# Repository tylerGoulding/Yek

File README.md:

# YEK
Yek is a prototype of an on-hand password manager that redefines how users interact with account safety and passwords on a laptop computer. It is an embedded device that acts as your personal butler to memorize passwords. With a yek device and a fingerprint scan, you can login to any of your accounts by connecting to any computer device through a bluetooth connection. Yek  acts as a keyboard and types in your login information (username and password) to the selected textbox of a login page, so that you do not have to remember your unique and strong passwords. It can fit in your pocket just like a physical keychain, and yet it can hold 63 of your accounts through a computer application.

## Team
- Fatema Almeshqab
- Tyler Goulding
- Matt Chu

## Code
When prototyping, we developed in Arduino then ported it to AVR C. We have included both for your convenience.

## PCB
The pcb was designed in Eagle. There is one error in the PCB if you are planning to send it out (or printing it in house if that's your slice of pie). The pins on the Battery JST plug are flipped. This is not a major issue but change it if you would like. We did not so that the professors could see our the equivalent PCB we printed.
## Computer Application
The computer application was written in Java and is available as a runnable .jar file that works on Windows, Mac, or Linux, and just requires that Java 8 be installed. The app, uses a library called jSerialComm to communicate with the Yek through a serial port connection.

## Building the Yek
### If you want to use Arduino
To build with Arduino:
Download the following libraries:

U8g2 Screen Library:
> https://github.com/olikraus/U8g2_Arduino

FRAM Library: 

> https://github.com/adafruit/Adafruit_FRAM_I2C

Fingerprint scanner:
> https://github.com/sparkfun/Fingerprint_Scanner-TTL

Bluefruit library:
> https://github.com/adafruit/Adafruit_BluefruitLE_nRF51

Open Arduino and compile the .ino in the folder Yek_arduino

### If you want to use GCC
Use the code in Yek_firmware folder

To build with GCC:

- install avr-gcc (GCC) 7.2.0 using your favorite package manager (this will take 2 hours... sorry)
- download LUFA
- update the path to lufa into makefile
- run make in the folder

## Acknowledgements
* Dean Camera, for LUFA.
* Adafruit (author hathach), for their parts and their BLE library
* Josh Hawley, for his FPS library
* Arduino, for their Print class and Stream class
* Olikraus, for the screen library and compressed fonts
* Zak Kemble, for a AVR implementation of millis
* Mike DiBacco, for helping us lasercut the case
* Some random dude at the Makerspace who helped me 3d print

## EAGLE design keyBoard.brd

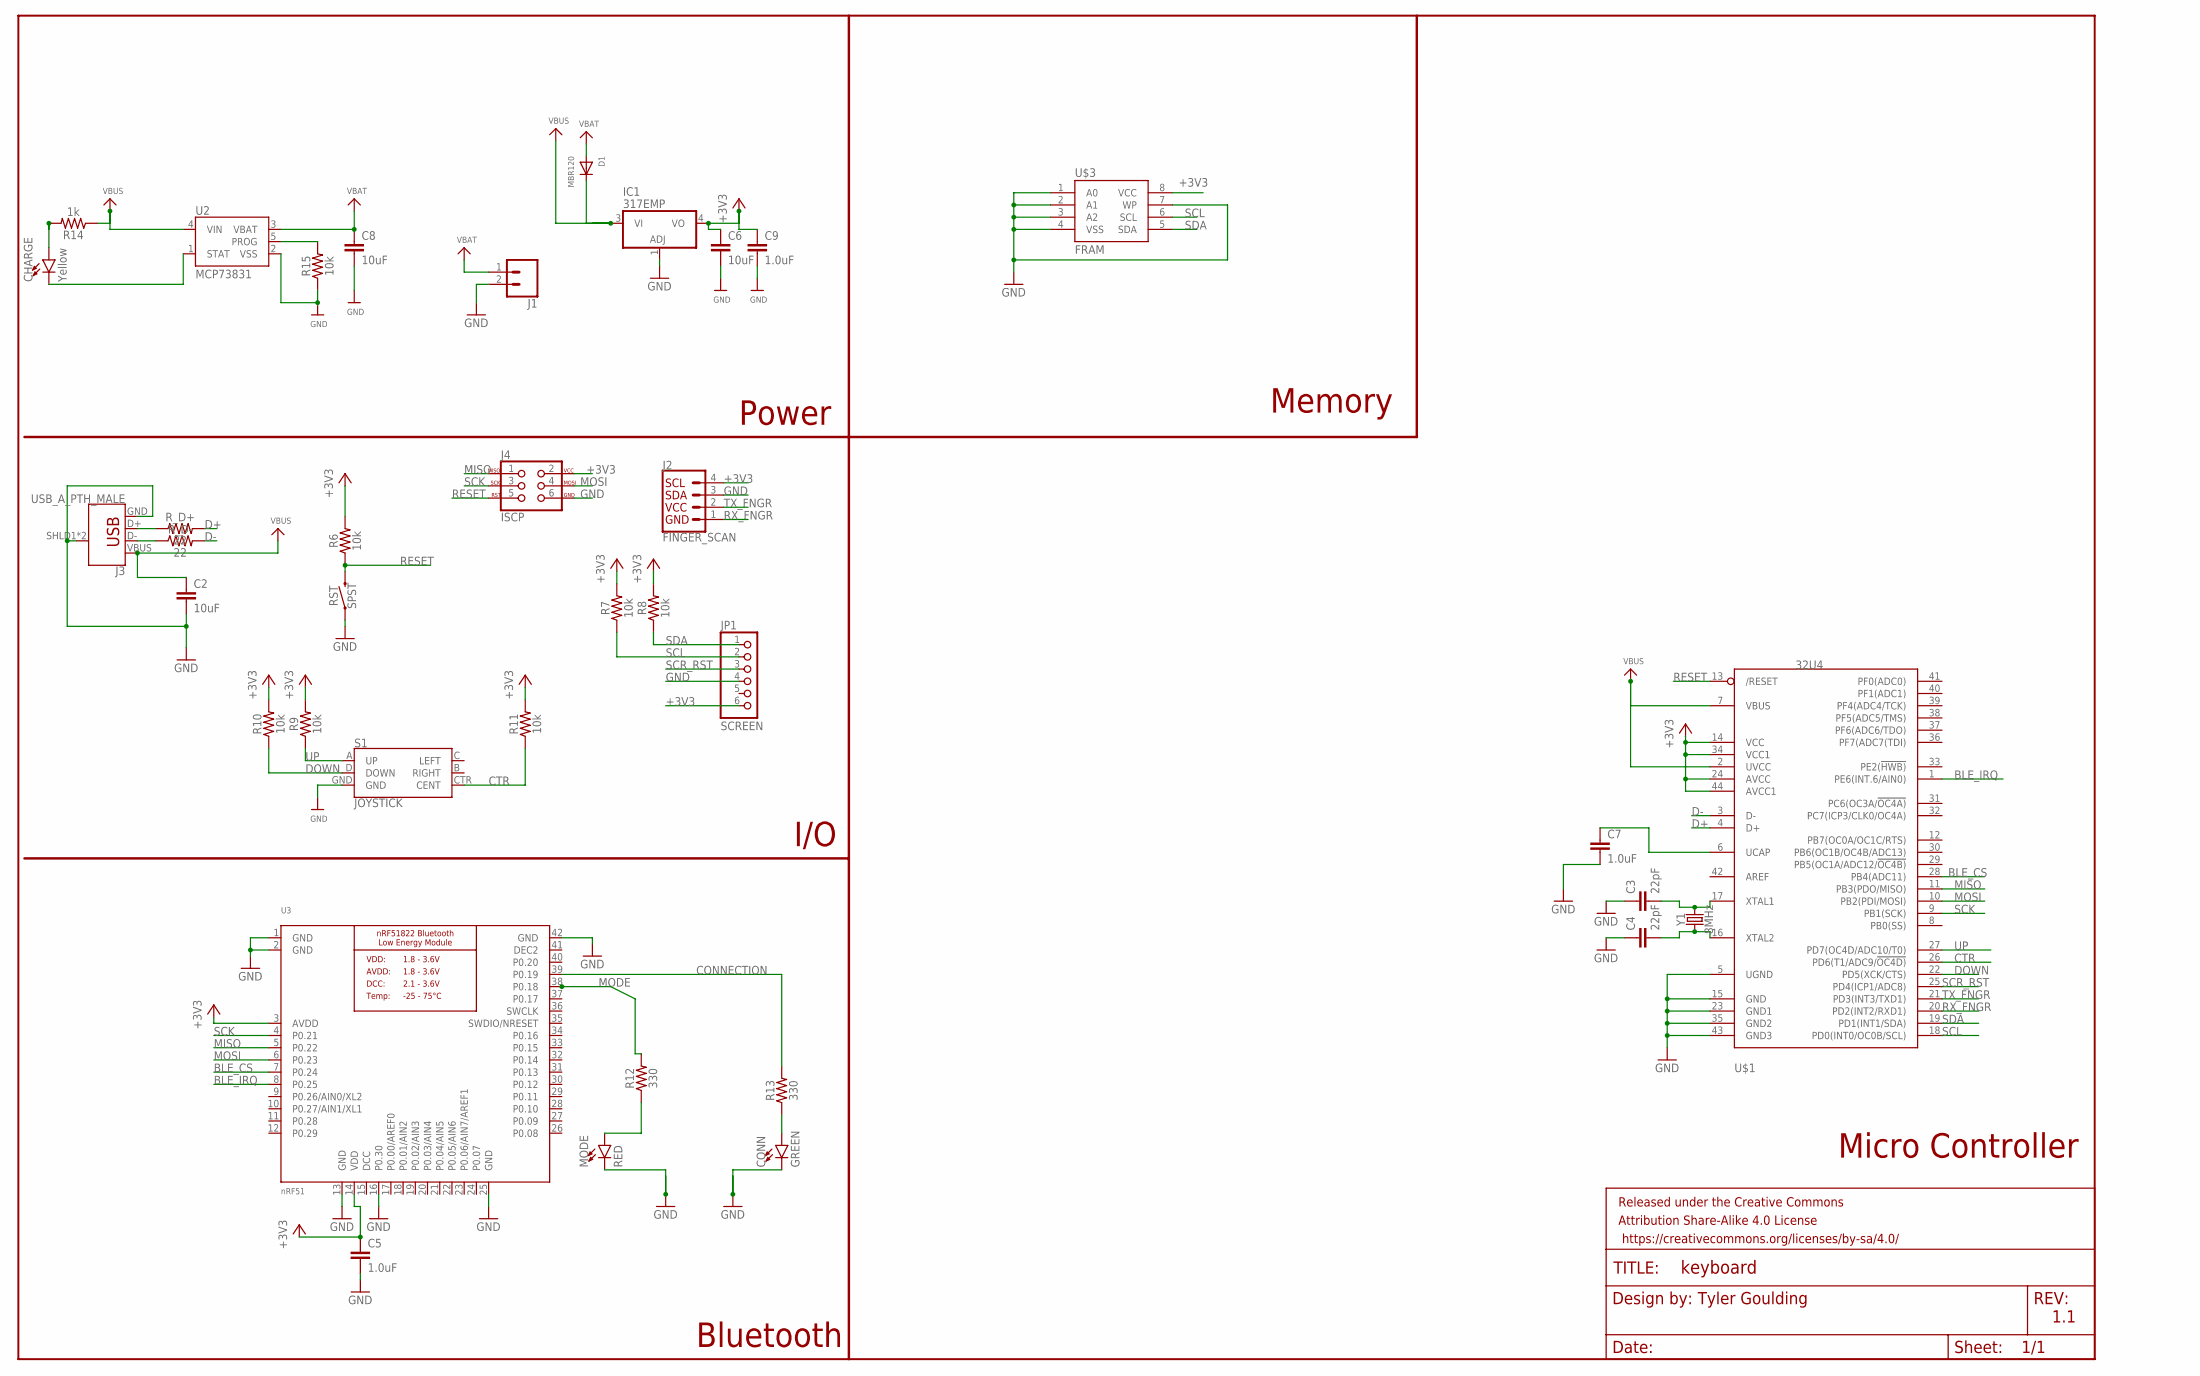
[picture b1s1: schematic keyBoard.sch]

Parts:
C2, C6, C8: 10uF; 0603
C3, C4: 22pF; 0603
C5, C7, C9: 1.0uF; 0603
CHARGE: Yellow; LED-0603
CONN: GREEN; LED-0603
D1: MBR120; SOD-123FL
FRAME1: FRAME-LEDGER; CREATIVE_COMMONS
IC1: 317EMP; SOT223
J1: CONN_02JST-PTH-2; JST-2-PTH
J2: FINGER_SCAN; 1X04_1MM_RA
J3: USB_A_PTH_MALE; USB-A-H
J4: ISCP; 2X3-NS
JP1: SCREEN; 1X06_ROUND
MODE: RED; LED-0603
R6, R7, R8, R9, R10, R11, R15: 10k; 0603
R12, R13: 330; 0603
R14: 1k; 0603
RST: SPST; TACTILE_SWITCH_SMD_4.5MM
R_D+: 22; 0603
R_D-: 22; 0603
S1: JOYSTICK; JOYSTICK_MINI
U2: MCP73831; SOT23-5
U3: nRF51; BLE_MODULE_RAYTAC_MDBT40
U$1: 32U4; TQFP44
U$3: FRAM; SOIC8
Y1: 8MHz; CRYSTAL-SMD-5X3.2-4PAD

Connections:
+3V3: C5.1, C6.1, C9.1, IC1.4 (VO), J2.4 (SCL), J4.2, JP1.6, R6.2, R7.2, R8.2, R9.2, R10.2, R11.2, U3.3 (AVDD), U3.14 (VDD), U$1.14 (VCC), U$1.24 (AVCC), U$1.34 (VCC1), U$1.44 (AVCC1), U$3.8 (VCC)
BLE_CS: U3.7 (P0.24), U$1.28 (PB4(ADC11))
BLE_IRQ: U3.8 (P0.25), U$1.1 (PE6(INT.6/AIN0))
CONNECTION: R13.2, U3.39 (P0.19)
CTR: R11.1, S1.CTR (CENT), U$1.26 (PD6(T1/ADC9/!OC4D))
D+: R_D+.2, U$1.4 (D+)
D-: R_D-.2, U$1.3 (D-)
DCC: U3.15 (DCC)
DEC2: U3.41 (DEC2)
DOWN: R10.1, S1.D (DOWN), U$1.22 (PD5(XCK/CTS))
GND: C2.2, C3.1, C4.1, C5.2, C6.2, C7.2, C8.2, C9.2, CONN.C, IC1.1 (ADJ), J1.2, J2.3 (SDA), J3.GND, J3.SHLD1 (SHIELD), J3.SHLD2 (SHIELD), J4.6, JP1.4, MODE.C, R15.1, RST.2 (1), RST.3 (1), S1.GND, U2.2 (VSS), U3.1 (GND), U3.2 (GND), U3.13 (GND), U3.16 (P0.30), U3.25 (GND), U3.42 (GND), U$1.5 (UGND), U$1.15 (GND), U$1.23 (GND1), U$1.35 (GND2), U$1.43 (GND3), U$3.1 (A0), U$3.2 (A1), U$3.3 (A2), U$3.4 (VSS), U$3.7 (WP)
MISO: J4.1, U3.5 (P0.22), U$1.11 (PB3(PDO/MISO))
MODE: R12.2, U3.38 (P0.18)
MOSI: J4.4, U3.6 (P0.23), U$1.10 (PB2(PDI/MOSI))
unnamed: CHARGE.A, R14.2
unnamed: J3.D+, R_D+.1
unnamed: J3.D-, R_D-.1
unnamed: MODE.A, R12.1
unnamed: R15.2, U2.5 (PROG)
unnamed: CONN.A, R13.1
RESET: J4.5, R6.1, RST.1 (2), RST.4 (2), U$1.13 (/RESET)
RX_FNGR: J2.1 (GND), U$1.20 (PD2(INT2/RXD1))
SCK: J4.3, U3.4 (P0.21), U$1.9 (PB1(SCK))
SCL: JP1.2, R7.1, U$1.18 (PD0(INT0/OC0B/SCL)), U$3.6 (SCL)
SCR_RST: JP1.3, U$1.25 (PD4(ICP1/ADC8))
SDA: JP1.1, R8.1, U$1.19 (PD1(INT1/SDA)), U$3.5 (SDA)
STAT: CHARGE.C, U2.1 (STAT)
TX_FNGR: J2.2 (VCC), U$1.21 (PD3(INT3/TXD1))
UCAP: C7.1, U$1.6 (UCAP)
UP: R9.1, S1.A (UP), U$1.27 (PD7(OC4D/ADC10/T0))
VBAT: C8.1, D1.A, J1.1, U2.3 (VBAT)
VBUS: C2.1, D1.C, IC1.3 (VI), J3.VBUS, R14.1, U2.4 (VIN), U$1.2 (UVCC), U$1.7 (VBUS)
XTAL1: C3.2, U$1.17 (XTAL1), Y1.3 (2)
XTAL2: C4.2, U$1.16 (XTAL2), Y1.1

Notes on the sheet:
Power
Bluetooth
I/O
Memory
Micro Controller
Tyler Goulding
1.1

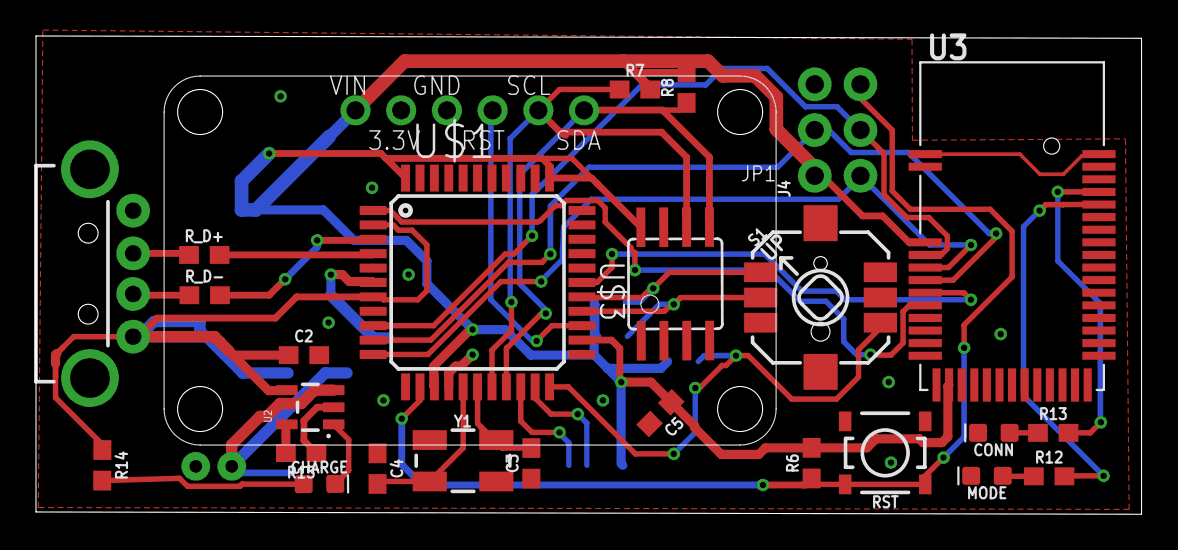
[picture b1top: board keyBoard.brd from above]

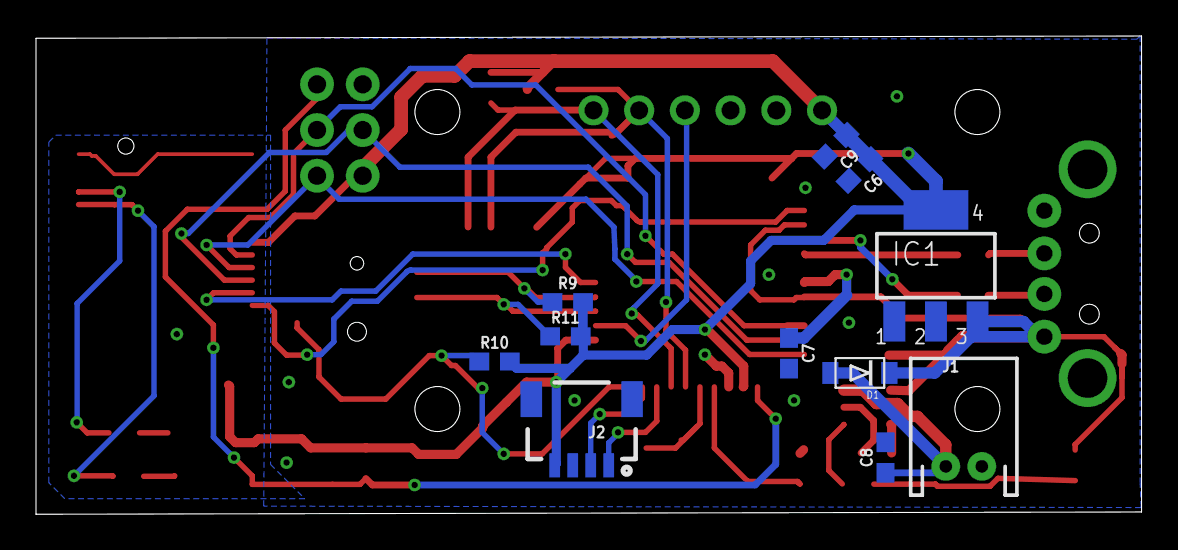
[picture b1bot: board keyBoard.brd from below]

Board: 2 copper layers, 61.4 x 26.6 mm, 38 parts (11 on the bottom side), 32 nets.

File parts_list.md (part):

| Part   | Value          | Device                          | Package                  | Description                                                                                                     | PROD_ID    | SF_ID     | SF_SKU    | SKU       | VALUE  |   |
|--------|----------------|---------------------------------|--------------------------|-----------------------------------------------------------------------------------------------------------------|------------|-----------|-----------|-----------|--------|---|
| C2     | 10uF           | 10UF-0603-6.3V-20%              | 0603                     | 10.0µF ceramic capacitors                                                                                       | CAP-11015  |           |           |           | 10uF   |   |
| C3     | 22pF           | 22PF-0603-50V-5%                | 0603                     | 22pF ceramic capacitors                                                                                         | CAP-07876  |           |           |           | 22pF   |   |
| C4     | 22pF           | 22PF-0603-50V-5%                | 0603                     | 22pF ceramic capacitors                                                                                         | CAP-07876  |           |           |           | 22pF   |   |
| C5     | 1.0uF          | 1.0UF-0603-16V-10%              | 0603                     | 1µF ceramic capacitors                                                                                          | CAP-00868  |           |           |           | 1.0uF  |   |
| C6     | 10uF           | 10UF-0603-6.3V-20%              | 0603                     | 10.0µF ceramic capacitors                                                                                       | CAP-11015  |           |           |           | 10uF   |   |
| C7     | 1.0uF          | 1.0UF-0603-16V-10%              | 0603                     | 1µF ceramic capacitors                                                                                          | CAP-00868  |           |           |           | 1.0uF  |   |
| C8     | 10uF           | 10UF-0603-6.3V-20%              | 0603                     | 10.0µF ceramic capacitors                                                                                       | CAP-11015  |           |           |           | 10uF   |   |
| C9     | 1.0uF          | 1.0UF-0603-16V-10%              | 0603                     | 1µF ceramic capacitors                                                                                          | CAP-00868  |           |           |           | 1.0uF  |   |
| CONN   | GREEN          | LED-GREEN0603                   | LED-0603                 | Green SMD LED                                                                                                   | DIO-00821  |           |           |           | GREEN  |   |
| D1     | MBR120         | DIODE_SOD-123FL                 | SOD-123FL                | Diode                                                                                                           |            |           |           |           |        |   |
| D4     | Yellow         | LED-YELLOW0603                  | LED-0603                 | Yellow SMD LED                                                                                                  | DIO-09003  |           |           |           | Yellow |   |
| FRAME1 | FRAME-LEDGER   | FRAME-LEDGER                    | CREATIVE_COMMONS         | Schematic Frame - Ledger                                                                                        |            |           |           |           |        |   |
| IC1    | 317EMP         | 317EMP                          | SOT223                   | Positive VOLTAGE REGULATOR                                                                                      |            |           |           |           |        |   |
| J1     |                | CONN_02JST-PTH-2                | JST-2-PTH                | Multi connection point. Often used as Generic Header-pin footprint for 0.1 inch spaced/style header connections | CONN-09863 |           |           | PRT-09914 |        |   |
| J2     | FINGER_SCAN    | QWIIC_CONNECTORJS-1MM           | 1X04_1MM_RA              | SparkFun I2C Standard Qwiic Connector                                                                           |            |           |           |           |        |   |
| J3     | USB_A_PTH_MALE | USB_A_PTH_MALE                  | USB-A-H                  | USB-A Connector                                                                                                 | CONN-08367 | PRT-00437 |           |           |        |   |
| J4     | ISCP           | AVR_SPI_PROG_3X2NS              | 2X3-NS                   | AVR ISP 6 Pin                                                                                                   |            |           |           |           |        |   |
| JP1    | SCREEN         | HEADER-1X6ROUND                 | 1X06_ROUND               | PIN HEADER                                                                                                      |            |           |           |           |        |   |
| MODE   | RED            | LED-RED0603                     | LED-0603                 | Red SMD LED                                                                                                     | DIO-00819  |           |           |           | RED    |   |
| R6     | 10k            | 10KOHM-0603-1/10W-1%            | 0603                     | 10kΩ resistor                                                                                                   | RES-00824  |           |           |           | 10k    |   |
| R7     | 10k            | 10KOHM-0603-1/10W-1%            | 0603                     | 10kΩ resistor                                                                                                   | RES-00824  |           |           |           | 10k    |   |
| R8     | 10k            | 10KOHM-0603-1/10W-1%            | 0603                     | 10kΩ resistor                                                                                                   | RES-00824  |           |           |           | 10k    |   |
| R9     | 10k            | 10KOHM-0603-1/10W-1%            | 0603                     | 10kΩ resistor                                                                                                   | RES-00824  |           |           |           | 10k    |   |
| R10    | 10k            | 10KOHM-0603-1/10W-1%            | 0603                     | 10kΩ resistor                                                                                                   | RES-00824  |           |           |           | 10k    |   |
| R11    | 10k            | 10KOHM-0603-1/10W-1%            | 0603                     | 10kΩ resistor                                                                                                   | RES-00824  |           |           |           | 10k    |   |
| R12    | 330            | 330OHM-0603-1/10W-1%            | 0603                     | 330Ω resistor                                                                                                   | RES-00818  |           |           |           | 330    |   |
| R13    | 330            | 330OHM-0603-1/10W-1%            | 0603                     | 330Ω resistor                                                                                                   | RES-00818  |           |           |           | 330    |   |
| R14    | 1k             | 1KOHM-0603-1/10W-1%             | 0603                     | 1kΩ resistor                                                                                                    | RES-07856  |           |           |           | 1k     |   |
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
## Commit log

2017-10-11 routing board
2017-10-21 updating board
2017-10-21 editted gitignore & deleted some files
2017-10-21 updated power circuit and layout
2017-10-21 removed some files
2017-10-21 update readme and added parts list
2017-10-22 forgot to connect DOWN on the joystick
2017-11-02 final board, mid-semester arduino proof of concept, non-working disjoint AVR C code
2017-12-02 Added GUI stuff
2017-12-03 finished Yek GUI, just need to fix style
2017-12-04 finished gui code, added runnable jar file
2017-12-10 adding all the code and some other stuff
2017-12-10 messed up the readme whoops

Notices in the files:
parts and their libraries:
SparkFun-LED: Licensing: Creative Commons ShareAlike 4.0 International - https://creativecommons.org/licenses/by-sa/4.0
SparkFun-Aesthetics: Released under the Creative Commons Attribution Share-Alike 4.0 License
SparkFun-Aesthetics: https://creativecommons.org/licenses/by-sa/4.0
